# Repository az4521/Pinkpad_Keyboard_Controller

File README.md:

# Pinkpad_Keyboard_Controller
 This repo contains all the files that are needed to make the [Pinkpad](https://crafty.moe/pinkpad.htm)'s thinkpad X61 keyboard controller.
 
 BOM:
```
1x 0543630489 connector
1x Teensy LC
2x BSS138 (or compatible) sot23 NFET
4x 0603 10K Resistor
2x 0.1uf 0603 Capacitor
```

If you'd like to order the unpopulated board directly, I recommend ordering [This OSHPark project](https://oshpark.com/shared_projects/3l395XbG)

This board is based on [HDR/USB_Laptop_Keyboard_Controller](https://github.com/HDR/USB_Laptop_Keyboard_Controller), I've just removed the need for a reset generator in exchange for getting rid of the caps lock LED.

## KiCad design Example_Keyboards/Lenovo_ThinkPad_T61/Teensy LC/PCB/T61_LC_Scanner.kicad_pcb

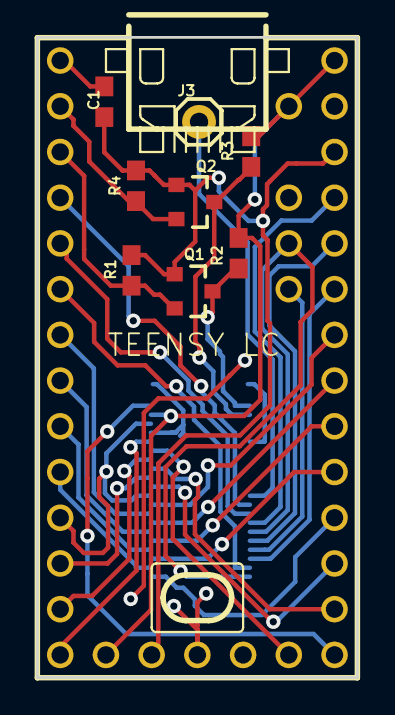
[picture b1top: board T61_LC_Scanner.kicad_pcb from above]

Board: 2 copper layers, 17.8 x 35.6 mm, 10 parts (0 on the bottom side), 33 nets.

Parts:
C1: 0.1uF; 0603
J1: WM6787CT-ND
J3: 3; 1X01
Q1, Q2: 220mA/50V/3.5Ω; SOT23-3
R1, R2, R3, R4: 10k; 0603
U1: TEENSY_LC

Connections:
unnamed: C1.1, Q1.1, Q2.1, R1.2, R4.2, U1.3V1, U1.3V2
unnamed: C1.2, J1.P$31, J1.P$34, J1.P$41, J1.P$42, J1.P$43, J1.P$44, U1.GND1, U1.GND2, U1.GND3
unnamed: J1.P$1, J1.P$11, U1.24
unnamed: J1.P$2, U1.16
unnamed: J1.P$3, U1.4
unnamed: J1.P$4, U1.8
unnamed: J1.P$5, U1.21
unnamed: J1.P$6, U1.17
unnamed: J1.P$7, U1.25
unnamed: J1.P$8, U1.7
unnamed: J1.P$9, U1.22
unnamed: J1.P$10, U1.18
unnamed: J1.P$12, U1.6
unnamed: J1.P$13, U1.23
unnamed: J1.P$14, U1.19
unnamed: J1.P$15, U1.3
unnamed: J1.P$16, U1.5
unnamed: J1.P$17, U1.2
unnamed: J1.P$18, U1.20
unnamed: J1.P$19, J3.1
unnamed: J1.P$20, J1.P$36, U1.9
unnamed: J1.P$22, U1.15
unnamed: J1.P$24, U1.10
unnamed: J1.P$26, U1.14
unnamed: J1.P$28, U1.11
unnamed: J1.P$30, U1.26
unnamed: J1.P$32, U1.12
unnamed: J1.P$37, Q2.3, R3.1
unnamed: J1.P$38, R2.2, R3.2, U1.5V, U1.VIN, U1.VUSB
unnamed: J1.P$39, Q1.3, R2.1
unnamed: J1.P$40, U1.13
unnamed: Q1.2, R1.1, U1.1
unnamed: Q2.2, R4.1, U1.0

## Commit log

2021-05-11 add pinkpad stuff
2021-05-11 reorganize
